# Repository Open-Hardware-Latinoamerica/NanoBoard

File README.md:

# NanoBoard
 Low cost board for educational robotics applications.
 
## Characteristics
The board has all the necessary hardware to assemble a robot for educational experiences:
- L293 to control two DC motors
- Connector for an HC-SR04 ultrasound distance meter
- Three on-board LEDs
- Three output connectors
- Two input connectors
- Buzzer
- Connector for a HC-05 type Bluetooth module

## Programming
The board can be programmed with any language available for Arduino Nano, although the circuit has been specially adapted to work with the *LOFI Blocks* app, which allows programming using blocks through the Bluetooth connection.

[LOFI Blocks features and required firmware](https://lofiblocks.com/en/)

## Design
The board was designed using [KiCad](https://kicad-pcb.org/) Ver. 4

---------------------------------------------------------------

# NanoBoard
Placa de bajo costo para aplicaciones de robótica educativa.

## Caracteristicas
La placa cuenta con todo el hardware necesario para montar un robot para experiencias educativas:

- L293 para controlar dos motores DC
- Conector para un medidor de distancias por ultrasonidos HC-SR04
- Tres LED integrados
- Tres conectores de salida
- Dos conectores de entrada
- Zumbador
- Conector para módulo Bluetooth tipo HC-05

## Programación
La placa se puede programar con cualquier lenguaje disponible para Arduino Nano, aunque el circuito ha sido especialmente adaptado para trabajar con la aplicación *LOFI Blocks*, que permite programar mediante bloques a través de la conexión Bluetooth.

[Funciones de LOFI Blocks y firmware requerido](https://lofiblocks.com/en/) 

## Diseño
La placa se diseñó con [KiCad](https://kicad-pcb.org/) Ver. 4

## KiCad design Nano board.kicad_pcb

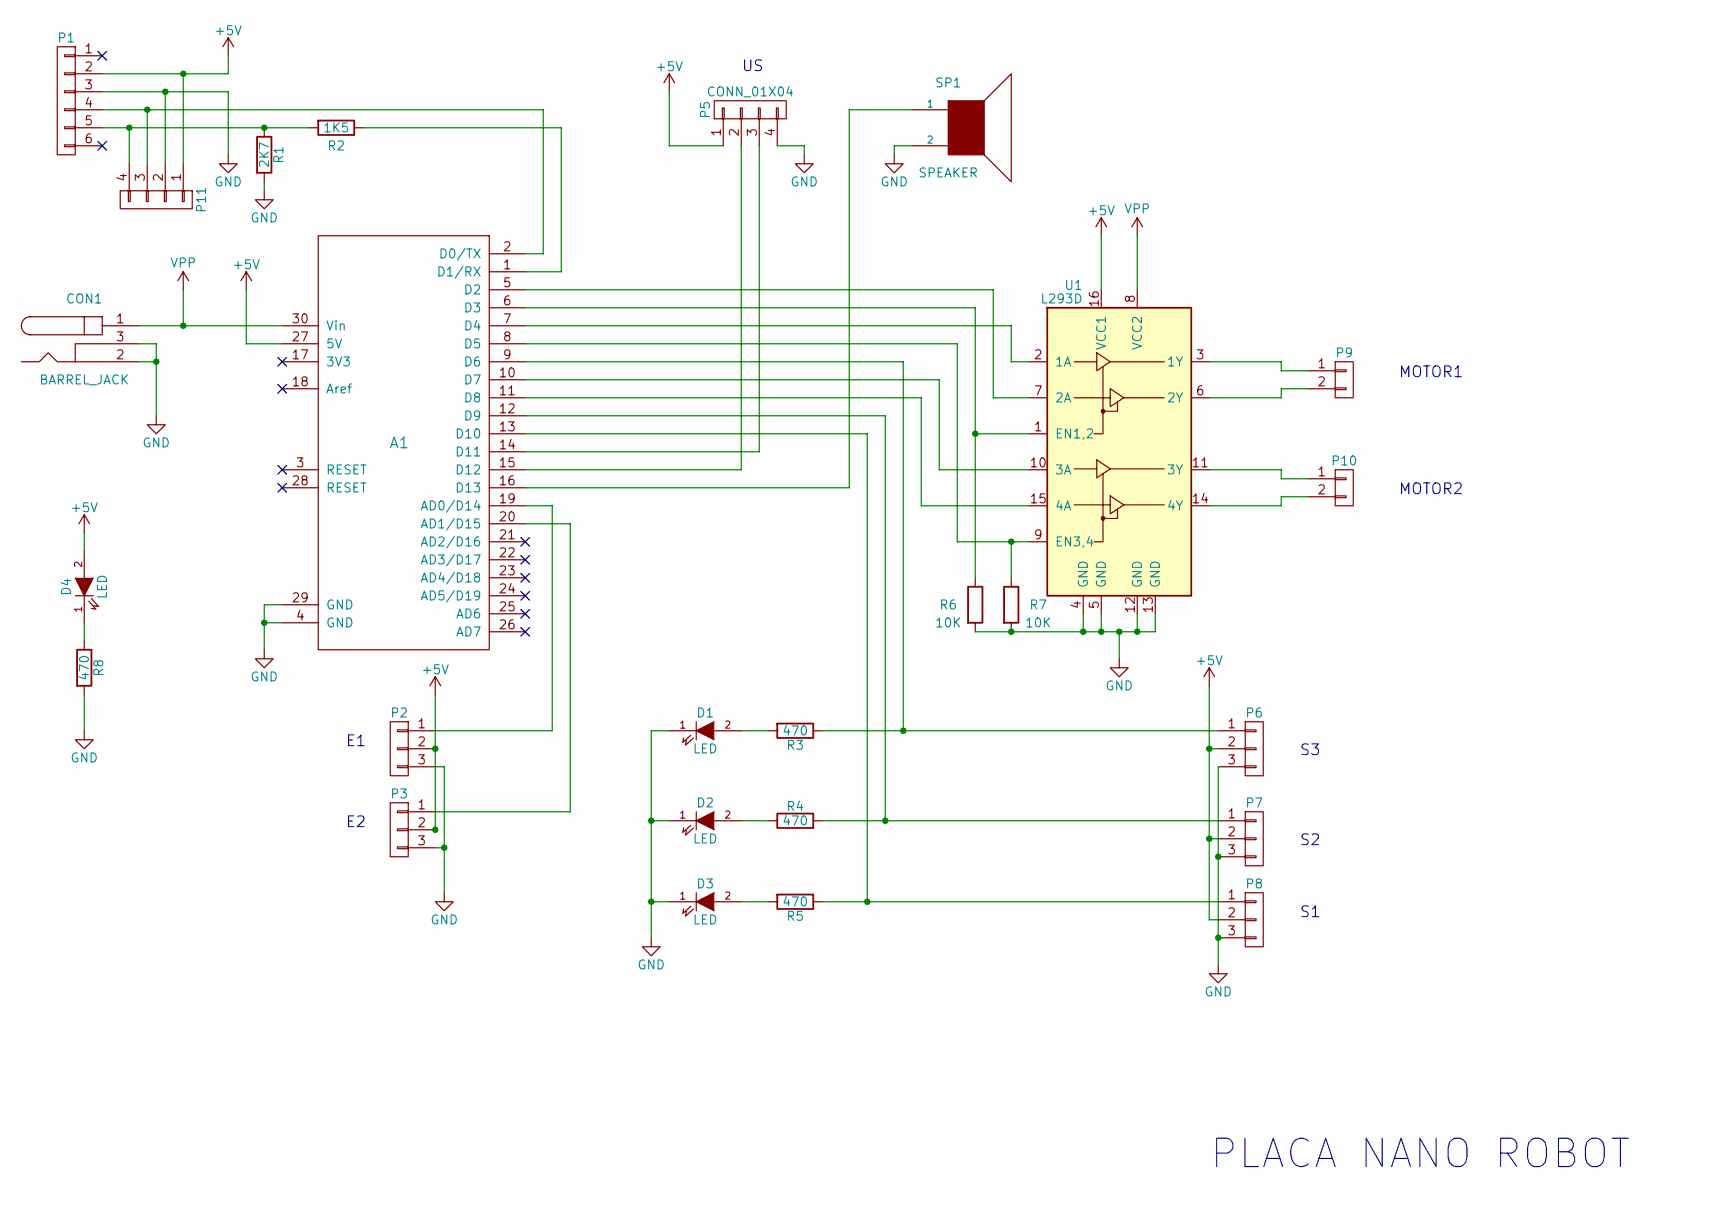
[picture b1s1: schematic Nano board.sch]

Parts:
A1: Arduino_Nano; arduino_nano
CON1: BARREL_JACK
D1, D2, D3, D4: LED; LED_D5.0mm
P1: CONN_01X06; PINHEAD1-6
P2, P3, P6, P7, P8: CONN_01X03; PINHEAD1-3
P5, P11: CONN_01X04; Socket_Strip_Straight_1x04_Pitch2.54mm
P9, P10: CONN_01X02; PINHEAD1-2
R1: 2K7; R_Axial_DIN0204_L3.6mm_D1.6mm_P7.62mm_Horizontal
R2: 1K5; R_Axial_DIN0204_L3.6mm_D1.6mm_P7.62mm_Horizontal
R3, R4, R5, R8: 470; R_Axial_DIN0204_L3.6mm_D1.6mm_P7.62mm_Horizontal
R6, R7: 10K; R_Axial_DIN0204_L3.6mm_D1.6mm_P7.62mm_Horizontal
SP1: SPEAKER; Buzzer_12x9.5RM7.6
U1: L293D; DIP-16_W7.62mm_LongPads

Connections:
+5V: A1.27 (5V), D4.2 (A), P1.2, P2.2, P3.2, P5.1, P6.2, P7.2, P8.2, P11.1, U1.16 (VCC1)
GND: A1.4 (GND), A1.29 (GND), CON1.2, CON1.3, D1.1 (K), D2.1 (K), D3.1 (K), P1.3, P2.3, P3.3, P5.4, P6.3, P7.3, P8.3, P11.2, R1.2, R6.2, R7.2, R8.2, SP1.2, U1.4 (GND), U1.5 (GND), U1.12 (GND), U1.13 (GND)
unnamed: A1.1 (D1/RX), R2.1
unnamed: A1.2 (D0/TX), P1.4, P11.3
unnamed: A1.5 (D2), U1.7 (2A)
unnamed: A1.6 (D3), R6.1, U1.1 (EN1,2)
unnamed: A1.7 (D4), U1.2 (1A)
unnamed: A1.8 (D5), R7.1, U1.9 (EN3,4)
unnamed: A1.9 (D6), P6.1, R3.1
unnamed: A1.10 (D7), U1.10 (3A)
unnamed: A1.11 (D8), U1.15 (4A)
unnamed: A1.12 (D9), P7.1, R4.2
unnamed: A1.13 (D10), P8.1, R5.1
unnamed: A1.14 (D11), P5.3
unnamed: A1.15 (D12), P5.2
unnamed: A1.16 (D13), SP1.1
unnamed: A1.19 (AD0/D14), P2.1
unnamed: A1.20 (AD1/D15), P3.1
unnamed: D1.2 (A), R3.2
unnamed: D2.2 (A), R4.1
unnamed: D3.2 (A), R5.2
unnamed: D4.1 (K), R8.1
unnamed: P1.5, P11.4, R1.1, R2.2
unnamed: P9.1, U1.3 (1Y)
unnamed: P9.2, U1.6 (2Y)
unnamed: P10.1, U1.11 (3Y)
unnamed: P10.2, U1.14 (4Y)
VPP: A1.30 (Vin), CON1.1, U1.8 (VCC2)

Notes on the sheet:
MOTOR1
MOTOR2
PLACA NANO ROBOT

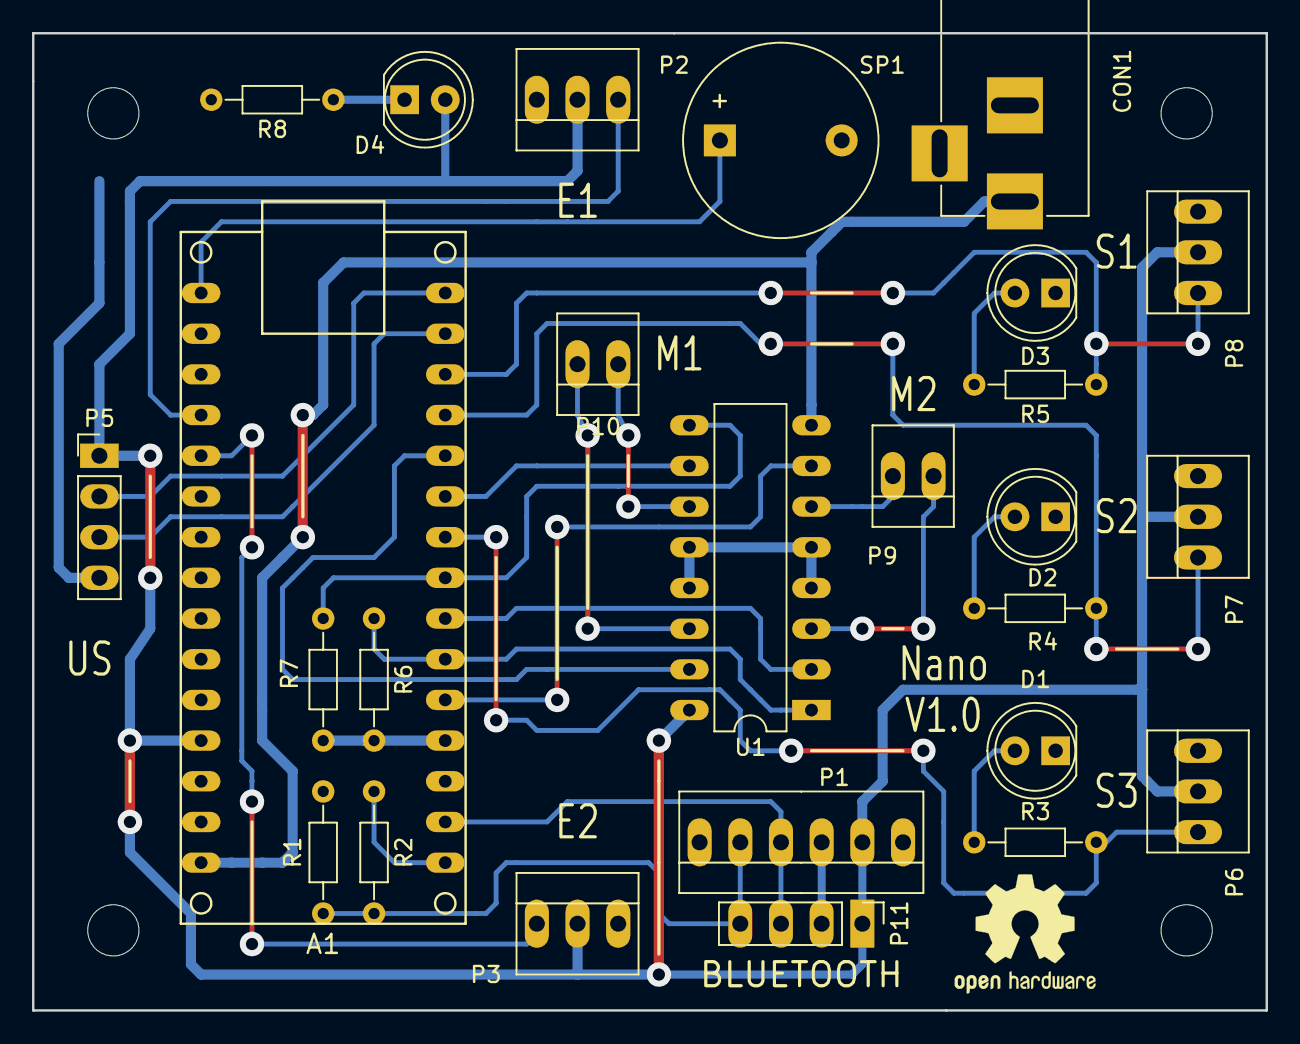
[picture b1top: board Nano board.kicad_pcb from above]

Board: 2 copper layers, 77.0 x 61.0 mm, 26 parts (0 on the bottom side), 28 nets.

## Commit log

2020-09-06 Create imagenes
2020-09-06 Create firmware
